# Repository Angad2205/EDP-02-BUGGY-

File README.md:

# EDP-02-BUGGY-
EDP-02 (BUGGY) SOURCE CODE AND FILES  - (TIET)

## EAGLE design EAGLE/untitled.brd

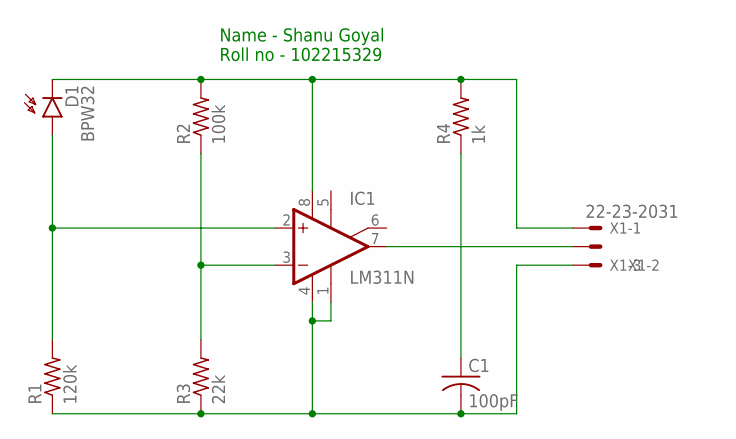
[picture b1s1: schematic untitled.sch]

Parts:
C1: 100pF; C025-050X050
D1: BPW32
IC1: LM311N; DIL08
R1: 120k; 0204/5
R2: 100k; 0204/5
R3: 22k; 0204/5
R4: 1k; 0204/5
X1: 22-23-2031

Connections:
unnamed: D1.K (C), IC1.8 (V+), R2.2, R4.2, X1.1
unnamed: C1.2, IC1.1 (GND), IC1.4 (V-), R1.1, R3.1, X1.3
unnamed: IC1.7 (OUT), X1.2
unnamed: C1.1, R4.1
unnamed: IC1.3 (-IN), R2.1, R3.2
unnamed: D1.A, IC1.2 (+IN), R1.2

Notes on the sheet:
Name - Shanu Goyal Roll no - 102215329

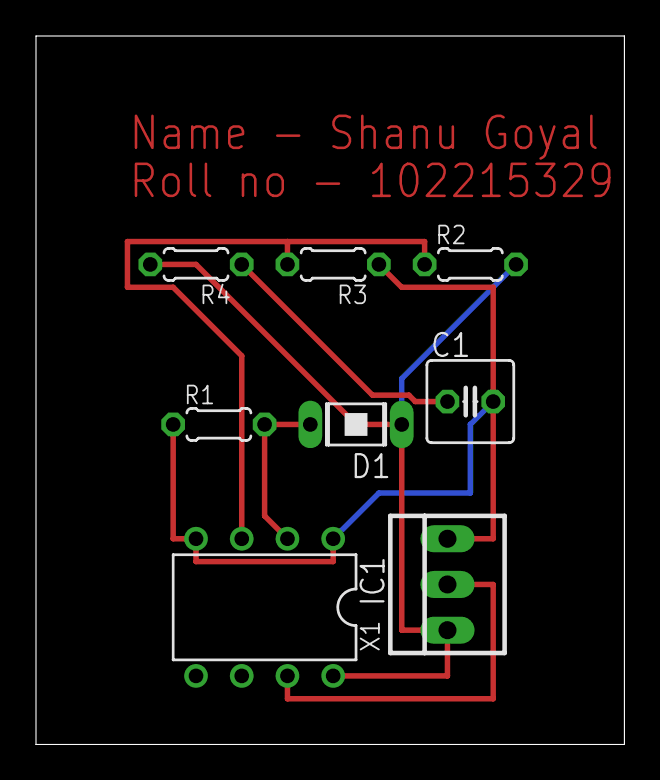
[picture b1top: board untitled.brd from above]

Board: 2 copper layers, 32.7 x 39.4 mm, 8 parts (0 on the bottom side), 6 nets.
